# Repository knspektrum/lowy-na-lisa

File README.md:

# Łowy na Lisa

Gra terenowa dla dzieci oparta na LoRa - polega na znalezieniu ukrytych nadajnikiów ("lisów") wykorzystując siłę sygnału radiowego

## O projekcie

"Łowy na Lisa" to otwarty projekt hardware'owy tworzący ręczne urządzenia do polowania na nadajniki LoRa. Każdy uczestnik otrzymuje kompaktowe urządzenie wyposażone w:

- Wyświetlacz OLED z animowaną mascotką lisa (szczęśliwy smutny w zależności od siły sygnału)
- Pasek 7 diod WS2812B pokazujących kierunek i siłę sygnału
- 4 przyciski do obsługi menu
- Obsługę baterii LiPo z ładowaniem przez USB-C
- Tryb głębokiego snu dla długiej pracy na baterii

### Hardware
- **MCU:** CubeCell HTCC-AM01
- **LEDy:** 7x WS2812B NeoPixel (adresowalne)
- **Wyświetlacz:** 0.96" OLED I2C
- **Przyciski:** 4x na boku
- **Zasilanie:** Bateria LiPo ~500mAh + ładowarka TP4054
- **USB:** USB-C z konwerterem CH340K (programowanie)
- **Antena:** 868MHz, Własnoręcznie stworzona przez nas antena yagi (wczesniej zewnętrzna antena yagi telewizyjna) 
- **Wymiary:** Podłużna obudowa przyjazna dla dzieci

## Wersje

- [Odbiornik na PCB (CubeCell)](#pcb) - docelowa wersja na własnej płytce
- [Nadajnik ESP32](software/fox-transmitter/README.md) - "lis": WeMos D1 R32 + HM-TRLR-D-TTL-868, zasilanie 5x AA
- [Odbiornik ESP32](software/led-receiver/README.md) - ESP32 + Seeed LoRa-E5 + 7 diod, zasilanie LiPo
- [Flota i aktualizacje](software/ota/README.md) - strona w Chrome: które urządzenia ESP32 są włączone, na jakim kanale i programie; podpisane aktualizacje przez Bluetooth

<details>
<summary><b>Odbiornik na PCB (CubeCell)</b> - schemat i plot</summary>

Plot  |  Schemat
:-------------------------:|:-------------------------:
  |  

Program: [software/receiver](software/receiver/receiver.ino)

</details>

<details>
<summary><b>Nadajnik ESP32</b> - schemat połączeń i kanały</summary>

D1 R32  |  HM-TRLR-D / baterie  |  Opis
:-------------------------:|:-------------------------:|:-------------------------
IO17 (TX)  |  RXD  |  komendy AT i dane do modułu
IO16 (RX)  |  TXD  |  odpowiedzi modułu
IO14  |  CONFIG  |  LOW = konfiguracja (AT), HIGH = nadawanie
5V  |  5V  |  zasilanie modułu
GND (górny, obok IO18)  |  GND (górny)  |
GND (dolny)  |  SLEEP  |  SLEEP na GND = moduł nie zasypia
VIN  |  + baterii 5x AA  |  ok. 7.5 V
GND (obok VIN)  |  - baterii  |

Id  |  Częstotliwość  |  Zworki CH_1-CH_4 (od góry)
:-------------------------:|:-------------------------:|:-------------------------:
1  |  863.0 MHz  |  ○ ○ ○ ○
2  |  863.5 MHz  |  ● ○ ○ ○
3  |  864.0 MHz  |  ○ ● ○ ○
4  |  864.5 MHz  |  ● ● ○ ○
5  |  865.0 MHz  |  ○ ○ ● ○
6  |  865.5 MHz  |  ● ○ ● ○
7  |  866.0 MHz  |  ○ ● ● ○
8  |  866.5 MHz  |  ● ● ● ○

Programowanie i szczegóły: [software/fox-transmitter](software/fox-transmitter/README.md)

</details>

<details>
<summary><b>Odbiornik ESP32</b> - schemat połączeń</summary>

ESP32  |  Element  |  Opis
:-------------------------:|:-------------------------:|:-------------------------
G33, G25  |  LED1, LED2 (czerwone)  |  rezystor 160 Ω
G26, G27, G14  |  LED3-LED5 (żółte)  |  rezystor 160 Ω
G12, G13  |  LED6, LED7 (zielone)  |  rezystor 30 Ω
G32  |  przycisk  |  drugi pin do GND
G17 (TX2)  |  LoRa-E5 RX (pad 9)  |  komendy AT
G16 (RX2)  |  LoRa-E5 TX (pad 10)  |  odpowiedzi i pakiety
3V3, GND  |  LoRa-E5 VCC (pad 1), GND (pad 2)  |
V5  |  wyłącznik → przetwornica 5 V → LiPo  |

Obsługa i programowanie: [software/led-receiver](software/led-receiver/README.md)

</details>

## PCB

Projekt PCB znajduje się w katalogu `pcb/` i jest przygotowany pod produkcję w JLCPCB (z PCBA assembly).

[Model 3D](pcb/lowy-na-lisa.stl)

Plot  |  Schemat
:-------------------------:|:-------------------------:
  |  

## Historia projektu

### Faza 1: Eksperymenty
- Testy modułów nRF905 - działają ale brak RSSI
- Przejście na moduły HM-TRLR-D-TTL-868 (LoRa/FSK/GFSK + RSSI)
- Brute-forceowanie komend AT modemu LoRa

### Faza 2: Targi Hobby
- Pierwsza działająca wersja
- Testy z dziećmi - obudowa sprawdza się, anteny za duże
- Problem: nadajniki się zakłócały (rozwiązane: różne kanały)
- Pozytywne wrażenia: światełka wzbudzają zainteresowanie

### Faza 3: PCB
- Projekt PCB zintegrowanego z modułem CubeCell
- Optymalizacja pod baterię (deep sleep, odcięcie LEDów)
- Przygotowanie pod produkcję SMT w JLCPCB

## Pomysły/Plany na rozwój

- **Tryby gry:**
  - Zdobywanie nadajników (zbliżenie się + potwierdzenie przyciskiem)
  - Rywalizacja (broadcast pozycji na innym kanale)
  - Tryb fabularny z questami

- **Animacje:**
  - Lis wyskakujący z krzaka przy zbliżeniu do nadajnika
  - Wizualizacja siły sygnału na ekranie i LEDach
  - Różne stany emocjonalne mascotki

- **Hardware:**
  - Własnoręcznie robione anteny DIY
  - Ulepszona obudowa z integracją PCB
  - Druk 3D

## Autorzy

- Hubert Mucha - Antena
- Antoni Sacewicz - Antena
- Judyta Ferenc - Antena
- Antoni Antosik - obudowa 3D
- Adrian Bruch - Animacje i interfejs ekranu
- Katarzyna Rybarkiewicz - Lider, Projekt PCB
- Maximilian Gaedig - Aktualny Lider, Projekt PCB, Software
# na rekrutacji

wiktor kandulski, discord: kandul - marketing, kolaboracja z harcerstwem
tymoteusz majorek, discord: tymoteuszu - materiały marketingowe/instrukcje - pisanie zaawansowane (pisał kśiążki), 3D
beata waligórska, discord: slaani. - animacje

## Licencja

GPLv3

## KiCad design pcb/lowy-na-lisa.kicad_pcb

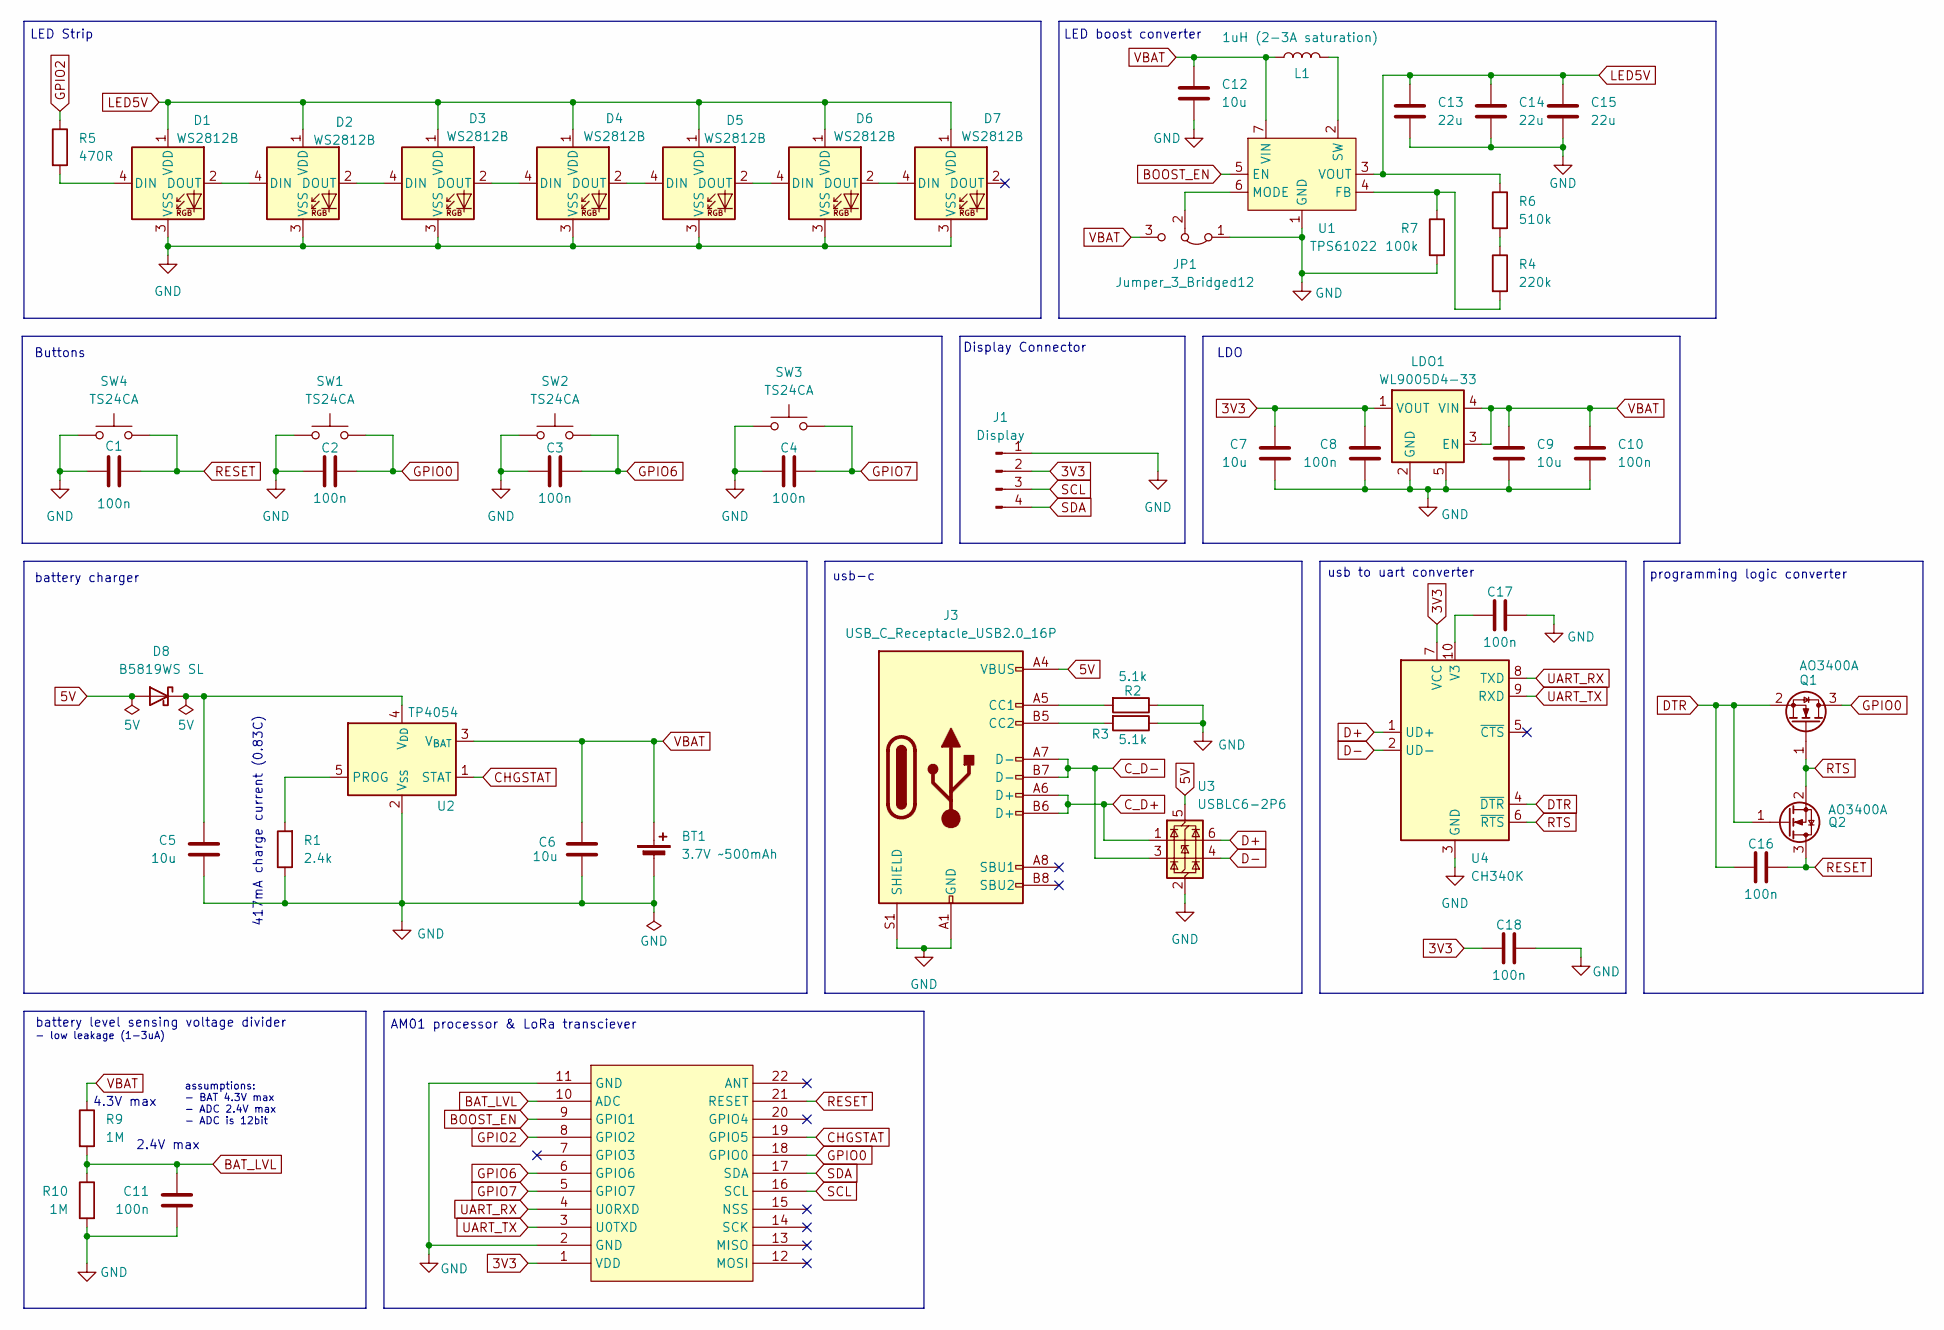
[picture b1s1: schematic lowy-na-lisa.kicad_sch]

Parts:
BT1: 3.7V ~500mAh; PinHeader_1x02_P2.54mm_Vertical
C1, C2, C3, C4, C8, C10, C11, C16, C17, C18: 100n; C_0402_1005Metric; LCSC C307331
C5, C6, C7, C9, C12: 10u; C_0603_1608Metric; LCSC C19702
C13, C14, C15: 22u; C_0603_1608Metric; LCSC C59461
D1, D2, D3, D4, D5, D6, D7: WS2812B; LED_WS2812B_PLCC4_5.0x5.0mm_P3.2mm; LCSC C48586674
D8: B5819WS SL; D_SOD-323; LCSC C7420331
HTCC-AM1: HTCC-AM01
J1: Display; PinHeader_1x04_P2.54mm_Vertical
J3: USB_C_Receptacle_USB2.0_16P; USB_C_Receptacle_G-Switch_GT-USB-7010ASV; LCSC C2988369
JP1: Jumper_3_Bridged12; SolderJumper-3_P1.3mm_Bridged2Bar12_Pad1.0x1.5mm
L1: 1uH (2-3A saturation); L_1008_2520Metric; LCSC C2849428
LDO1: WL9005D4-33; UDFN-4-1EP_1x1mm_P0.65mm_EP0.48x0.48mm; LCSC C5357206
Q1, Q2: AO3400A; SOT-23; LCSC C20917
R1: 2.4k; R_0603_1608Metric; LCSC C22940
R2, R3: 5.1k; R_0603_1608Metric; LCSC C23186
R4: 220k; R_0603_1608Metric; LCSC C22961
R5: 470R; R_0402_1005Metric; LCSC C25117
R6: 510k; R_0603_1608Metric; LCSC C23192
R7: 100k; R_0603_1608Metric; LCSC C25803
R9, R10: 1M; R_0402_1005Metric; LCSC C26083
SW1, SW2, SW3, SW4: TS24CA; SW_TS31-46-35-BK-B-160-RA-SMT-TR; LCSC C393942
U1: TPS61022; Texas_RWU0007A_VQFN-7_2x2mm_P0.5mm; LCSC C915088
U2: TP4054; SOT-23-5; LCSC C32574
U3: USBLC6-2P6; SOT-666; LCSC C2827693
U4: CH340K; SSOP-10-1EP_3.9x4.9mm_P1mm_EP2.1x3.3mm; LCSC C968586

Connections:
3V3: C7.1, C8.1, C18.1, HTCC-AM1.1 (VDD), J1.2, LDO1.1 (VOUT), U4.7 (VCC)
5V: D8.2 (A), J3.A4 (VBUS), J3.A9 (VBUS), J3.B4 (VBUS), J3.B9 (VBUS), U3.5 (VBUS)
BAT_LVL: C11.1, HTCC-AM1.10 (ADC), R9.2, R10.1
BOOST_EN: HTCC-AM1.9 (GPIO1), U1.5 (EN)
CHGSTAT: HTCC-AM1.19 (GPIO5), U2.1 (STAT)
C_D+: J3.A6 (D+), J3.B6 (D+), U3.1 (I/O1)
C_D-: J3.A7 (D-), J3.B7 (D-), U3.3 (I/O2)
D+: U3.6 (I/O1), U4.1 (UD+)
D-: U3.4 (I/O2), U4.2 (UD-)
DTR: C16.1, Q1.2 (S), Q2.1 (G), U4.4 (~DTR)
GND: BT1.2 (-), C1.1, C2.1, C3.1, C4.1, C5.2, C6.1, C7.2, C8.2, C9.2, C10.2, C11.2, C12.2, C13.2, C14.2, C15.2, C17.2, C18.2, D1.3 (VSS), D2.3 (VSS), D3.3 (VSS), D4.3 (VSS), D5.3 (VSS), D6.3 (VSS), D7.3 (VSS), HTCC-AM1.2 (GND), HTCC-AM1.11 (GND), J1.1, J3.A1 (GND), J3.A12 (GND), J3.B1 (GND), J3.B12 (GND), J3.S1 (SHIELD), JP1.1 (A), LDO1.2 (GND), LDO1.5, R1.1, R2.1, R3.1, R7.2, R10.2, SW1.1, SW2.1, SW3.1, SW4.1, U1.1 (GND), U2.2 (V_{SS}), U3.2 (GND), U4.3 (GND), U4.11 (GND)
GPIO0: C2.2, HTCC-AM1.18 (GPIO0), Q1.3 (D), SW1.2
GPIO2: HTCC-AM1.8 (GPIO2), R5.1
GPIO6: C3.2, HTCC-AM1.6 (GPIO6), SW2.2
GPIO7: C4.2, HTCC-AM1.5 (GPIO7), SW3.2
LED5V: C13.1, C14.1, C15.1, D1.1 (VDD), D2.1 (VDD), D3.1 (VDD), D4.1 (VDD), D5.1 (VDD), D6.1 (VDD), D7.1 (VDD), R6.1, U1.3 (VOUT)
unnamed: D1.4 (DIN), R5.2
unnamed: D1.2 (DOUT), D2.4 (DIN)
unnamed: D2.2 (DOUT), D3.4 (DIN)
unnamed: D3.2 (DOUT), D4.4 (DIN)
unnamed: D4.2 (DOUT), D5.4 (DIN)
unnamed: D5.2 (DOUT), D6.4 (DIN)
unnamed: D6.2 (DOUT), D7.4 (DIN)
unnamed: C5.1, D8.1 (K), U2.4 (V_{DD})
unnamed: J3.A5 (CC1), R2.2
unnamed: J3.B5 (CC2), R3.2
unnamed: JP1.2 (C), U1.6 (MODE)
unnamed: R4.1, R6.2
unnamed: R4.2, R7.1, U1.4 (FB)
unnamed: L1.2, U1.2 (SW)
unnamed: R1.2, U2.5 (PROG)
unnamed: C17.1, U4.10 (V3)
RESET: C1.2, C16.2, HTCC-AM1.21 (RESET), Q2.3 (D), SW4.2
RTS: Q1.1 (G), Q2.2 (S), U4.6 (~RTS)
SCL: HTCC-AM1.16 (SCL), J1.3
SDA: HTCC-AM1.17 (SDA), J1.4
UART_RX: HTCC-AM1.4 (U0RXD), U4.8 (TXD)
UART_TX: HTCC-AM1.3 (U0TXD), U4.9 (RXD)
VBAT: BT1.1 (+), C6.2, C9.1, C10.1, C12.1, JP1.3 (B), L1.1, LDO1.3 (EN), LDO1.4 (VIN), R9.1, U1.7 (VIN), U2.3 (V_{BAT})

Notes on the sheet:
usb to uart converter
LED Strip
LDO
Buttons
2.4V max
- low leakage (1-3uA)
programming logic converter
assumptions: - BAT 4.3V max - ADC 2.4V max - ADC is 12bit
battery level sensing voltage divider
LED boost converter
usb-c
417mA charge current (0.83C)
Display Connector
4.3V max
AM01 processor & LoRa transciever
battery charger

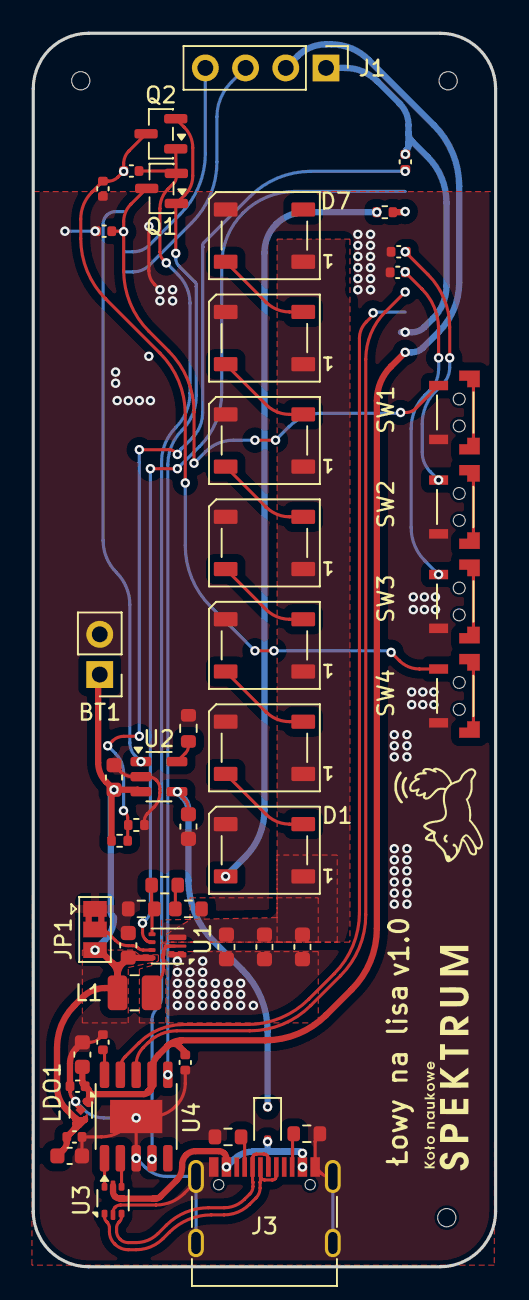
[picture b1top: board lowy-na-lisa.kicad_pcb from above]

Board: 2 copper layers, 29.2 x 77.9 mm, 52 parts (1 on the bottom side), 39 nets.

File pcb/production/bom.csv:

Designator,Footprint,Quantity,Value,LCSC Part #
BT1,PinHeader_1x02_P2.54mm_Vertical,1,3.7V ~500mAh,
"C1, C10, C11, C16, C17, C18, C2, C3, C4, C8",0402,10,100n,C307331
"C12, C5, C6, C7, C9",0603,5,10u,C19702
"C13, C14, C15",0603,3,22u,C59461
"D1, D2, D3, D4, D5, D6, D7",LED_WS2812B_PLCC4_5.0x5.0mm_P3.2mm,7,WS2812B,C48586674
D8,D_SOD-323,1,B5819WS SL,C7420331
HTCC-AM1,HTCC-AM01,1,~,
J1,PinHeader_1x04_P2.54mm_Vertical,1,Display,
J3,USB_C_Receptacle_G-Switch_GT-USB-7010ASV,1,USB_C_Receptacle_USB2.0_16P,C2988369
L1,1008,1,1uH (2-3A saturation),C2849428
LDO1,UDFN-4-1EP_1x1mm_P0.65mm_EP0.48x0.48mm,1,WL9005D4-33,C5357206
"Q1, Q2",SOT-23,2,AO3400A,C20917
R1,0603,1,2.4k,C22940
"R10, R9",0402,2,1M,C26083
"R2, R3",0603,2,5.1k,C23186
R4,0603,1,220k,C22961
R5,0402,1,470R,C25117
R6,0603,1,510k,C23192
R7,0603,1,100k,C25803
"SW1, SW2, SW3, SW4",SW_TS31-46-35-BK-B-160-RA-SMT-TR,4,TS24CA,C393942
U1,Texas_RWU0007A_VQFN-7_2x2mm_P0.5mm,1,TPS61022,C915088
U2,SOT-23-5,1,TP4054,C32574
U3,SOT-666,1,USBLC6-2P6,C2827693
U4,SSOP-10-1EP_3.9x4.9mm_P1mm_EP2.1x3.3mm,1,CH340K,C968586

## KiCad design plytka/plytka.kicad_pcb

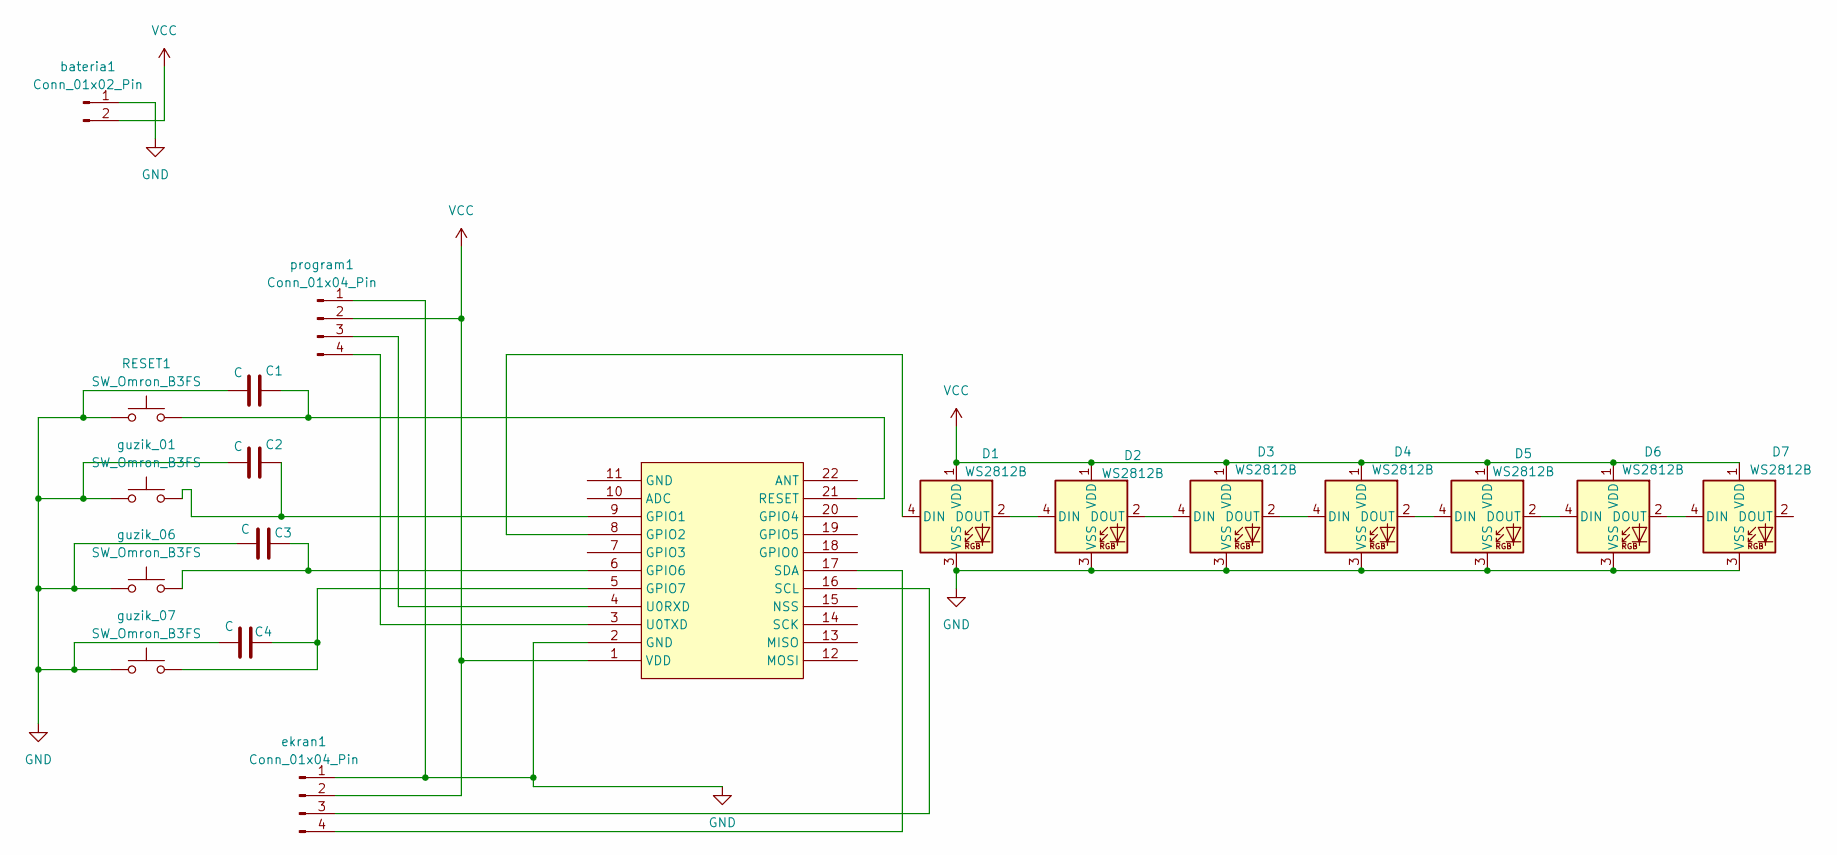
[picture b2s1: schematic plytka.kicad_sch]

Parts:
C1, C2, C3, C4: C; C_0402_1005Metric
D1, D2, D3, D4, D5, D6, D7: WS2812B; LED_WS2812B_PLCC4_5.0x5.0mm_P3.2mm
HTCC-AM1: HTCC-AM01
RESET1: SW_Omron_B3FS; SW_SPST_Omron_B3FS-100xP
bateria1: Conn_01x02_Pin; PinHeader_1x02_P2.54mm_Vertical
ekran1: Conn_01x04_Pin; PinHeader_1x04_P2.54mm_Vertical
guzik_01, guzik_06, guzik_07: SW_Omron_B3FS; SW_SPST_Omron_B3FS-100xP
program1: Conn_01x04_Pin; PinHeader_1x04_P2.54mm_Vertical

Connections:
GND: C1.1, C2.1, C3.1, C4.1, D1.3 (VSS), D2.3 (VSS), D3.3 (VSS), D4.3 (VSS), D5.3 (VSS), D6.3 (VSS), D7.3 (VSS), HTCC-AM1.2 (GND), RESET1.1, bateria1.1, ekran1.1, guzik_01.1, guzik_06.1, guzik_07.1, program1.1
unnamed: D1.4 (DIN), HTCC-AM1.8 (GPIO2)
unnamed: D1.2 (DOUT), D2.4 (DIN)
unnamed: D2.2 (DOUT), D3.4 (DIN)
unnamed: D3.2 (DOUT), D4.4 (DIN)
unnamed: D4.2 (DOUT), D5.4 (DIN)
unnamed: D5.2 (DOUT), D6.4 (DIN)
unnamed: D6.2 (DOUT), D7.4 (DIN)
unnamed: C2.2, HTCC-AM1.9 (GPIO1), guzik_01.2
unnamed: C3.2, HTCC-AM1.6 (GPIO6), guzik_06.2
unnamed: C4.2, HTCC-AM1.5 (GPIO7), guzik_07.2
unnamed: C1.2, HTCC-AM1.21 (RESET), RESET1.2
unnamed: HTCC-AM1.16 (SCL), ekran1.3
unnamed: HTCC-AM1.17 (SDA), ekran1.4
unnamed: HTCC-AM1.4 (U0RXD), program1.3
unnamed: HTCC-AM1.3 (U0TXD), program1.4
VCC: D1.1 (VDD), D2.1 (VDD), D3.1 (VDD), D4.1 (VDD), D5.1 (VDD), D6.1 (VDD), D7.1 (VDD), HTCC-AM1.1 (VDD), bateria1.2, ekran1.2, program1.2

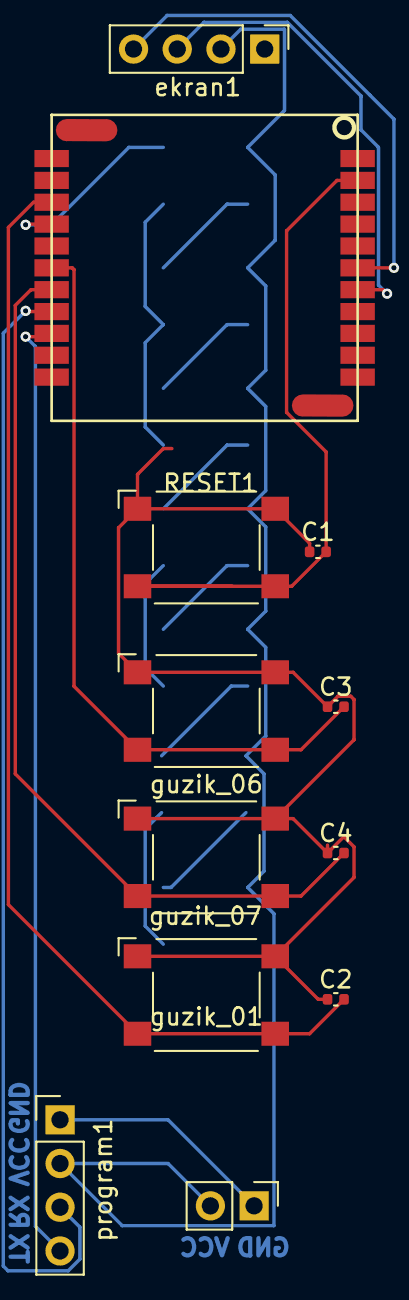
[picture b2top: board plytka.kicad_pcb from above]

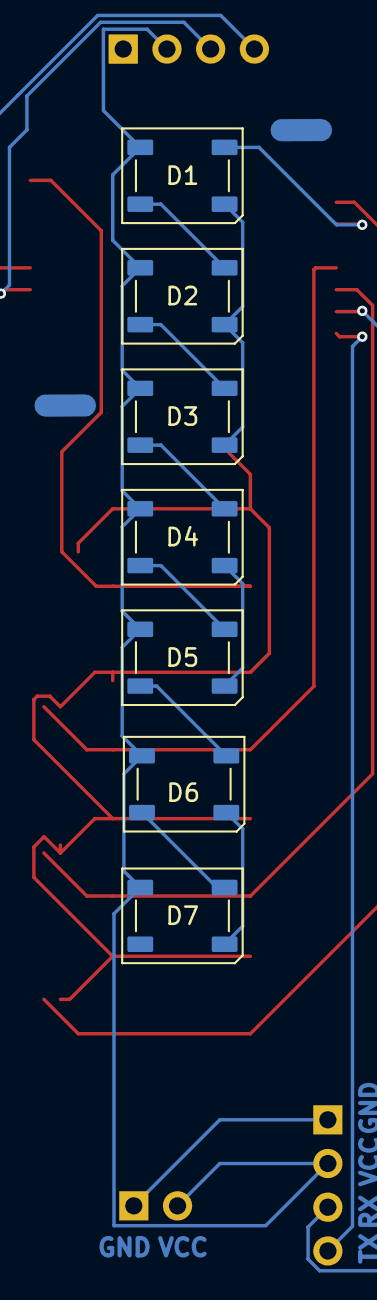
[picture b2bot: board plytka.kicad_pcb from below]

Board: 2 copper layers, 19 parts (7 on the bottom side), 17 nets.

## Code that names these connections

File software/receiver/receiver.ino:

#include "LoRaWan_APP.h"
#include "sx126x.h"
#include "Arduino.h"
#include "CubeCell_NeoPixel.h"
#include <Wire.h>
#include "HT_SSD1306Wire.h" 



#define BASE_RF_FREQUENCY 863000000  // Hz
#define FREQUENCY_STEP 500000

#define TX_OUTPUT_POWER 14  // dBm

#define LORA_BANDWIDTH 0         // [0: 125 kHz, \
                                 //  1: 250 kHz, \
                                 //  2: 500 kHz, \
                                 //  3: Reserved]
#define LORA_SPREADING_FACTOR 7  // [SF7..SF12]
#define LORA_CODINGRATE 1        // [1: 4/5, \
                                 //  2: 4/6, \
                                 //  3: 4/7, \
                                 //  4: 4/8]
#define LORA_PREAMBLE_LENGTH 8   // Same for Tx and Rx
#define LORA_SYMBOL_TIMEOUT 0    // Symbols
#define LORA_FIX_LENGTH_PAYLOAD_ON false
#define LORA_IQ_INVERSION_ON false


#define RX_TIMEOUT_VALUE 1000
#define BUFFER_SIZE 30  // Define the payload size here

#define LED_BOOST_ON GPIO1
#define LED_DATA GPIO2
#define SW1 GPIO0
#define SW2 GPIO6
#define SW3 GPIO7
#define BAT_LVL ADC

SSD1306Wire  display(0x3c, 500000, SDA, SCL, GEOMETRY_128_64, NULL); // addr , freq , SDA, SCL, resolution , rst
CubeCell_NeoPixel pixels(7, LED_DATA, NEO_GRB + NEO_KHZ800);



char txpacket[BUFFER_SIZE];
char rxpacket[BUFFER_SIZE];

static RadioEvents_t RadioEvents;
static TimerEvent_t sleep;

int16_t rssi, rxSize;

bool lora_idle = true;
bool powered_on = false;

uint8_t sync_word[8] = { 0xCA, 0xFE, 0x00, 0x00, 0x00, 0x00, 0xBA, 0xBE };


void setup() {
  Serial.begin(115200);
  Serial.println("Hej liski!");

  pinMode(SW1, INPUT_PULLUP);

  pinMode(LED_BOOST_ON,OUTPUT);
  digitalWrite(LED_BOOST_ON,HIGH);
  pixels.begin();
  pixels.clear();

  for (int i = 0; i < 2; i++) {
    for (int j = 0; j < 7; j++) {
      display_bits_on_leds(to_first_led_bits(j));
      delay(50);
    }
    for (int j = 0; j < 7; j++) {
      display_bits_on_leds(to_last_led_bits(8 - j));
      delay(50);
    }
  }
  // Show initial display buffer contents on the screen --
  // the library initializes this with an Adafruit splash screen.
  display.display();
  delay(2000); // Pause for 2 seconds

  // Clear the buffer
  display.clear();

  // Draw a single pixel in white
  display.setPixel(10, 10);

  // Show the display buffer on the screen. You MUST call display() after
  // drawing commands to make them visible on screen!
  display.display();

  display_bits_on_leds(0);

  rssi = 0;

  RadioEvents.RxDone = on_rx_done;
  Radio.Init(&RadioEvents);
  Radio.SetChannel(BASE_RF_FREQUENCY);



  Radio.SetRxConfig(MODEM_LORA, LORA_BANDWIDTH, LORA_SPREADING_FACTOR,
                    LORA_CODINGRATE, 0, LORA_PREAMBLE_LENGTH,
                    LORA_SYMBOL_TIMEOUT, LORA_FIX_LENGTH_PAYLOAD_ON,
                    0, true, 0, 0, LORA_IQ_INVERSION_ON, true);

  set_transmitter_id(1);
}


void loop() {
  if (powered_on && digitalRead(SW1) == LOW) {
    detachInterrupt(SW1);
    handle_button_press();
  }

  if (!powered_on) {
    
    sx126xSleep();
    while (digitalRead(SW1) == LOW)
      ;
    delay(50); // debounce
    attachInterrupt(SW1, on_wake, FALLING);
    Serial.println();
    Serial.flush();
    lowPowerHandler();
  }

  if (powered_on && lora_idle) {
    lora_idle = false;
    Serial.println("into RX mode");
    Radio.Rx(0);
  }
}

void on_rx_done(uint8_t *payload, uint16_t size, int16_t rssi, int8_t snr) {
  if (size < 2) {
    Serial.println("WARN: packet of size 0 or 1 recieved");
    Radio.Sleep();
    lora_idle = true;
    return;
  }

  if ((payload[0] != get_transmitter_id()) || (payload[1] != get_transmitter_id())) {
    Radio.Sleep();
    lora_idle = true;
    return;
  }

  if (size > 29)
    size = 29;

  memcpy(rxpacket, payload, size);
  rxpacket[size] = '\0';

  rssi = rssi;
  rxSize = size;
  display_strength_on_leds((110 + rssi) / (110 / 7));
  Serial.printf("received packet \"%s\" with rssi=%d snr=%d length=%d packet_tx_id=%d\r\n", rxpacket, rssi, snr, rxSize, rxpacket[1]);


  Radio.Sleep();
  lora_idle = true;
}

void handle_button_press() {
  int press_start = millis();
  delay(50);  // debounce
  if (digitalRead(SW1) == LOW) {
    int i = 1;
    
    while (digitalRead(SW1) == LOW) {
      if (millis() - press_start > 2500) {  // if pressed for longer than 2.5 seconds
        powered_on = false;
        i = (i + 1) % 8;
        display_bits_on_leds(1 << i);
        delay(30);
      }

      delay(5);
    };

    if (!powered_on) {
      display_bits_on_leds(0);
      Serial.println("powered off");
      for (int j = 0; j < 8; j++) {
        display_bits_on_leds(to_first_led_bits((7-j)));
        delay(300);
      }
      return;
    }

    set_transmitter_id(1 + (get_transmitter_id() % 6));
    Serial.printf("\r\nChanged transmitter id to %d\r\n", get_transmitter_id());

    Radio.Sleep();
    lora_idle = true;

    display_bits_on_leds(to_first_led_bits(get_transmitter_id()));
    delay(500);
    display_bits_on_leds(0);
  }
}

void on_wake() {
  if (!powered_on) {
    powered_on = true;

    Serial.println("woke up!");
    while (digitalRead(SW1) == LOW)
      ;
  }
}

void set_transmitter_id(uint8_t id) {
  for (int i = 0; i < 4; i++) {
    sync_word[i + 2] = id;
  }

  SX126xSetSyncWord(sync_word);
  Radio.SetChannel(BASE_RF_FREQUENCY+(id-1)*FREQUENCY_STEP);
}

uint8_t get_transmitter_id() {
  return sync_word[2];
}

void display_bits_on_leds(int8_t bits) {
  for (int i = 0; i < 7; i++) {
    uint32_t color;

    if ((bits & (1 << i)) > 0) {
      color = pixels.Color(20, 20, 20);
    }else {
      color = pixels.Color(0, 0, 0);
    }
    
    pixels.setPixelColor(i, color);
  }
  pixels.show();
}

uint8_t to_last_led_bits(uint8_t x) {
  if (x >= 8) return 0xFF;
  return ((1u << x) - 1u);
}

uint8_t to_first_led_bits(uint8_t x) {
  if (x == 0) return 0;
  if (x >= 8) return 0xFF;
  x += 1;
  return ((1u << x) - 1u) << (8 - x);
}

void display_strength_on_leds(int8_t strength) {
  display_bits_on_leds(to_last_led_bits(strength));
}

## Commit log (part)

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2025-11-12 switch to d1 r32 pin layout + board
2025-11-22 hoperf
2025-11-22 bruteforce
2026-03-10 add pcb
2026-03-10 pcb update
2026-03-12 pcb: add TPS61022 boost converter and simplify battery monitoring
    - Add TPS61022 boost converter
    - Simplify battery voltage sensing by removing DIVFET1 switched divider
    - Update voltage divider values, now 1M and 1M + cap for stabilizing
    - Add mode selection jumper for PFM/PWM switching
    - Update battery capacity to ~500mAh
2026-03-12 update fp cache kicad
2026-03-14 aktualna wersja
2026-03-15 cleanup
2026-03-15 footprints
2026-03-15 fix lineendings
2026-03-15 miau
2026-03-15 footprint
2026-03-20 lcsc
2026-03-28 almost finish pcb
2026-03-28 smol fixy
2026-03-29 dopiesczenie:)
2026-03-29 git instrukcja
2026-03-29 nonchalant zaokronglenia
2026-03-29 final final final??
2026-03-29 add production files to git
2026-03-30 pcb: rename project, final touches, cleanup
2026-03-30 export 3d models as step
2026-03-30 add presentation resources
2026-03-30 docs
2026-03-30 fix: readme image links
2026-03-30 rearrange readme
2026-03-30 readme update
2026-03-30 update authors
2026-03-30 update image and license
2026-03-30 embed stl model in readme
